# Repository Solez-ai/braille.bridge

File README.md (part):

<div align="center">

# BrailleBridge (BB1)

**Open-Source Bilingual English & Bharati Bangla Wireless Mechanical Braille Chording System**

*Hardware v3 · BB1 Wiring Board PCB v4 · Decode-on-Release ESP32 Firmware · PyQt6 Desktop Teacher Suite · Kotlin Jetpack Compose Android App · Web Bluetooth & Web Serial Console*

<p>

</p>

<p>
  <a href="https://brailebridge.vercel.app/"><strong>Live Web Application</strong></a> ·
  <a href="https://solez-ai.mintlify.app"><strong>Technical Documentation</strong></a> ·
  <a href="https://github.com/solez-ai/braille.bridge/releases/latest"><strong>Download Desktop EXE & Android APK</strong></a> ·
  <a href="hardware/bb1_wiring_board_v4/exports/jlcpcb_gerbers_v4.zip"><strong>JLCPCB Gerber Package (v4)</strong></a> ·
  <a href="BrailleBridge_Technical_Documentation.pdf"><strong>Engineering Monograph (PDF)</strong></a>
</p>

<br />

</div>

---

## Table of Contents

1. [Executive Overview](#1-executive-overview)
2. [Comparative Benchmark Against Legacy Assistive Systems](#2-comparative-benchmark-against-legacy-assistive-systems)
3. [Institutional Field Testing & Validation](#3-institutional-field-testing--validation)
   - [3.1 BERDO — Blind Education and Rehabilitation Development Organization](#31-berdo--blind-education-and-rehabilitation-development-organization)
   - [3.2 University of Dhaka — Resource Centre for the Visually Impaired Students (Co-Sponsored by Sightsavers)](#32-university-of-dhaka--resource-centre-for-the-visually-impaired-students-co-sponsored-by-sightsavers)
4. [Mechanical Hardware & 3D-Printed Wedge Enclosure (v3)](#4-mechanical-hardware--3d-printed-wedge-enclosure-v3)
   - [4.1 Physical Layout & Ergonomic Geometry](#41-physical-layout--ergonomic-geometry)
   - [4.2 Multi-Angle Hardware Gallery](#42-multi-angle-hardware-gallery)
   - [4.3 Bill of Materials (BOM) & Direct GPIO Architecture](#43-bill-of-materials-bom--direct-gpio-architecture)
5. [Custom Commercial PCB — BB1 Wiring Board v4 (KiCad 10)](#5-custom-commercial-pcb--bb1-wiring-board-v4-kicad-10)
   - [5.1 Raytraced 3D Renders & 2D Copper Composite](#51-raytraced-3d-renders--2d-copper-composite)
   - [5.2 Full KiCad 10 Schematic Diagram](#52-full-kicad-10-schematic-diagram)
   - [5.3 Dual-Mode Buck-Boost Power Architecture & Global Manufacturing Flexibility](#53-dual-mode-buck-boost-power-architecture--global-manufacturing-flexibility)
   - [5.4 Physical Stackup, Netlist Verification & Pin Allocation](#54-physical-stackup-netlist-verification--pin-allocation)
6. [ESP32 Firmware & Chording State Machine](#6-esp32-firmware--chording-state-machine)
   - [6.1 Six-Dot Bitmask Encoding](#61-six-dot-bitmask-encoding)
   - [6.2 Decode-on-Release Algorithm & Temporal Guards](#62-decode-on-release-algorithm--temporal-guards)
   - [6.3 Dual-Transport ASCII vs. Multi-Byte UTF-8 Rule](#63-dual-transport-ascii-vs-multi-byte-utf-8-rule)
   - [6.4 Structured Telemetry & Host Command Protocol](#64-structured-telemetry--host-command-protocol)
7. [Bilingual Grade 1 English & Bharati Bangla Dictionaries](#7-bilingual-grade-1-english--bharati-bangla-dictionaries)
8. [Multi-Platform Software Ecosystem](#8-multi-platform-software-ecosystem)
   - [8.1 System Architecture](#81-system-architecture)
   - [8.2 Native Desktop Teacher Suite (Python / PyQt6 / Bleak / WinRT / PySerial)](#82-native-desktop-teacher-suite-python--pyqt6--bleak--winrt--pyserial)
   - [8.3 Android Companion Application (Kotlin 2.2 / Jetpack Compose / Room)](#83-android-companion-application-kotlin-22--jetpack-compose--room)
   - [8.4 Web Platform, Interactive 3D/2D PCB Inspector & Virtual Chord Pad](#84-web-platform-interactive-3d2d-pcb-inspector--virtual-chord-pad)
9. [Repository Structure](#9-repository-structure)
10. [Build, Flash & Fabrication Guide](#10-build-flash--fabrication-guide)
11. [License & Citation](#11-license--citation)

---

## 1. Executive Overview

Across South Asia and the developing world, visually impaired students face a severe Structural Scribal Dependency during high-stakes public and university examinations. Because traditional mechanical Perkins Braillers produce embossed paper scripts that sighted examiners cannot read—and commercial refreshable Braille displays cost between **$1,500 and $3,500+ USD**—students are forced to dictate answers verbally to human scribes. A human scribe filters the student's literacy, spelling accuracy, mathematical notation, and pacing through a third party.

**BrailleBridge (BB1)** eliminates scribal dependency for less than **$15 USD** in total hardware cost (**~$11.70 USD** in raw components).

1. **Tactile Mechanical Input**: The student types standard 6-dot Braille chords on eight full-travel **Outemu Red linear mechanical switches** (`45 gf` actuation force, `2.0 mm` pre-travel, `4.0 mm` total travel, `50M`-cycle rating) housed in a tool-free, 3D-printed PLA wedge chassis with an ergonomic `7.1°` typing slope.
2. **Deterministic Decode-on-Release Engine**: An **ESP32-WROOM-32** dual-core microcontroller samples all eight switch channels directly via internal pull-up resistors (`INPUT_PULLUP`), accumulating a 6-bit chord bitmask (`0x01`–`0x3F`) across the downstroke and decoding the complete chord at the exact microsecond all keys are released (`15 ms` contact-bounce filter, live-tunable `5–50 ms`, supporting **100+ WPM** rapid chording).
3. **Bilingual Grade 1 English & Bharati Bangla**: A single `500 ms` hold of Dots `4+5+6` toggles between standard **Grade 1 English Braille** and **6-dot Bharati Bangla Braille** (স্বরবর্ণ vowels, ব্যঞ্জনবর্ণ consonants, কার dependent vowel signs via `Shift` layer, numerals `0–9`, and mathematical operators), totaling **54 base mappings** plus shifted layers.
4. **Simultaneous Sighted & Auditory Output**: Every decoded chord streams simultaneously over **Bluetooth Low Energy HID**, **BLE Nordic UART Service (NUS)**, and **USB Serial (`115200` baud)** to sighted teachers' screens (in print English, Bangla, or **128 real-time translated languages**) while local offline Text-to-Speech (`pyttsx3` / SAPI5 / Android TTS / Web Speech API) speaks every letter, word, and UI event back to the blind student.

---

## 2. Comparative Benchmark Against Legacy Assistive Systems

| Engineering Metric | Human Exam Scribe | Mechanical Perkins Brailler | Commercial Refreshable Display | **BrailleBridge (BB1 v3 / PCB v4)** |
| :--- | :--- | :--- | :--- | :--- |
| **Unit Cost (USD)** | Recurring per-exam fee | $750 – $950 USD | $1,500 – $3,500+ USD | **~$11.70 BOM (<$15 complete)** |
| **Student Independence** | None (verbal dictation) | High (embossed paper only) | High | **100% direct student authorship** |
| **Sighted Teacher Readability** | Sighted scribe handwriting | Unreadable without Braille training | Requires proprietary host software | **Instant live print text + 128-language translation** |
| **Bharati Bangla + English** | Depends on scribe fluency | Manual embossing only | Rarely supported natively | **Hardware chord toggle (`Dots 4+5+6` hold, `500 ms`)** |
| **Acoustic Noise Profile** | Verbal noise (requires isolated room) | ~75–80 dBA impact embossing | ~55 dBA piezoelectric pins | **~42 dBA silent linear switches (mainstream classroom safe)** |
| **Chording Speed Ceiling** | Limited by dictation speed | ~40–60 WPM mechanical return | ~60–80 WPM | **100+ WPM (`15 ms` decode-on-release state machine)** |
| **Power Architecture** | N/A | Purely mechanical | Proprietary sealed Li-Po pack | **USB-C + 4×AA (Direct Bypass or 5 V Buck-Boost Module)** |
| **Repairability & CAD/PCB** | N/A | Factory specialist overhaul | Sealed proprietary assembly | **100% Open-Source (GPL-3.0 STL + KiCad 10 PCB + Firmware)** |

---

## 3. Institutional Field Testing & Validation

BrailleBridge was evaluated directly in institutional environments in Dhaka, Bangladesh with visually impaired learners, university students, and assistive education pioneers.

### 3.1 BERDO — Blind Education and Rehabilitation Development Organization

Field validation was conducted at the **Blind Education and Rehabilitation Development Organization (BERDO)** headquarters in Rupnagar, Mirpur, Dhaka, under the supervision of BERDO Founder and Executive Director **Md. Saidul Huq**—recipient of the **2026 Independence Award (Swadhinata Puruskar)**, Bangladesh's highest civilian state honor, and the **2023 Ekushey Padak**. Visually impaired students and educators tested the 8-switch mechanical tactile profile, bilingual Bharati Bangla chording, and real-time voice synthesis.

<div align="center">
<table>
  <tr>
    <td align="center" width="50%">
      
      <br />
      <sub><strong>Fig 3.1a:</strong> Institutional demonstration with Md. Saidul Huq (Founder &amp; Executive Director, BERDO; 2026 Swadhinata Puruskar &amp; 2023 Ekushey Padak laureate).</sub>
    </td>
    <td align="center" width="50%">
      
      <br />
      <sub><strong>Fig 3.1b:</strong> Tactile evaluation of the 8-switch mechanical Perkins layout inside the BERDO Braille library in Mirpur, Dhaka.</sub>
    </td>
  </tr>
  <tr>
    <td align="center" width="50%">
      
      <br />
      <sub><strong>Fig 3.1c:</strong> Real-time bilingual English and Bharati Bangla chording trial with live desktop telemetry.</sub>
    </td>
    <td align="center" width="50%">
      
      <br />
      <sub><strong>Fig 3.1d:</strong> Assessing Outemu Red 45 gf actuation consistency and decode-on-release responsiveness.</sub>
    </td>
  </tr>
</table>

<p>
  
</p>
</div>

### 3.2 University of Dhaka — Resource Centre for the Visually Impaired Students (Co-Sponsored by Sightsavers)

BrailleBridge was benchmarked side-by-side against mechanical Perkins Braillers at the **Resource Centre for the Visually Impaired Students** inside the **Dhaka University Central Library** (Kazi Nazrul Islam Ave, Dhaka). Established in **2007** and jointly sponsored by **Dhaka University Library** and **Sightsavers**, the Resource Centre serves visually impaired undergraduates and researchers across the university.

<div align="center">
<table>
  <tr>
    <td align="center" width="50%">
      
      <br />
      <sub><strong>Fig 3.2a:</strong> Resource Centre for the Visually Impaired Students at Dhaka University Central Library (Jointly Sponsored by Dhaka University Library &amp; Sightsavers).</sub>
    </td>
    <td align="center" width="50%">
      
      <br />
      <sub><strong>Fig 3.2b:</strong> Direct ergonomic and acoustic benchmark of BrailleBridge BB1 alongside a mechanical Perkins Brailler at Dhaka University.</sub>
    </td>
  </tr>
  <tr>
    <td align="center" width="50%">
      
      <br />
      <sub><strong>Fig 3.2c:</strong> Visually impaired student testing wireless 6-dot chording and auditory TTS confirmation at the Dhaka University Resource Centre.</sub>
    </td>
    <td align="center" width="50%">
      
      <br />
      <sub><strong>Fig 3.2d:</strong> Guided finger-placement transition from heavy mechanical embossing levers to low-force 45 gf linear mechanical switches.</sub>
    </td>
  </tr>
</table>

<p>
  
</p>
</div>

---

## 4. Mechanical Hardware & 3D-Printed Wedge Enclosure (v3)

### 4.1 Physical Layout & Ergonomic Geometry

The BB1 v3 enclosure (`180 mm × 80 mm` footprint, tapering from `30 mm` front wall height to `40 mm` rear wall height) forms a `7.1°` angled wedge engineered for neutral wrist posture during extended exam sessions. The top plate mounts **eight `14.0 × 14.0 mm` MX-compatible mechanical switch cutouts** arranged in a symmetric split-hand Perkins Braille arc:

```text
+-----------------------------------------------------------------------+
|                       REAR INTEGRATED HINGE                           |
|                                                                       |
|     [ Dot 3 ]   [ Dot 2 ]   [ Dot 1 ]   [ Dot 4 ]   [ Dot 5 ]   [ Dot 6 ]
|      GPIO 27     GPIO 14     GPIO 12     GPIO 26     GPIO 25     GPIO 33
|      (Ring L)   (Middle L)  (Index L)   (Index R)   (Middle R)  (Ring R)
|                                                                       |
|                   [ SPACE ]               [ SHIFT / BKSP ]            |
|                    GPIO 32                    GPIO 23                 |
|                   (Thumb L)                  (Thumb R)                |
|                                                                       |
|             [ SNAP LATCH L ]             [ SNAP LATCH R ]             |
+-----------------------------------------------------------------------+
```

- **Zero External Indicator LEDs**: In keeping with blind-first hardware design, the BB1 v3 architecture eliminates physical indicator LEDs and current-limiting resistor harnesses entirely. All operational feedback (character readout, backspace confirmation, language switching, capital lock state, and BLE pairing status) is delivered through multi-platform auditory speech synthesis and tactile landmarking.
- **Clamshell Serviceability**: A print-in-place rear hinge (`2.2 mm` filament/steel pin) paired with dual front snap latches allows teachers or technicians to open the top plate in seconds without removing screws.
- **Underside Tool-Free `4×AA` Battery Bay**: A drop-out bottom hatch (`120 × 62 mm`) provides immediate external access to the `4×AA` battery holder while isolating the internal PCB cavity.

### 4.2 Multi-Angle Hardware Gallery

<div align="center">
<table>
  <tr>
    <td align="center" width="50%">
      
      <br />
      <sub><strong>Fig 4.2a:</strong> Top isometric render showing the 6-dot ergonomic finger arc and dual thumb modifier keys (`SPACE` and `SHIFT / BKSP`).</sub>
    </td>
    <td align="center" width="50%">
      
      <br />
      <sub><strong>Fig 4.2b:</strong> Front elevation detailing the Outemu Red keycap profile and dual front snap-latch seam.</sub>
    </td>
  </tr>
  <tr>
    <td align="center" width="50%">
      
      <br />
      <sub><strong>Fig 4.2c:</strong> Quarter-angle view highlighting the `30 mm` to `40 mm` (`7.1°`) ergonomic wedge slope.</sub>
    </td>
    <td align="center" width="50%">
      
      <br />
      <sub><strong>Fig 4.2d:</strong> Close-up of the `14 × 14 mm` plate-mounted Outemu Red linear switches (`45 gf` actuation).</sub>
    </td>
  </tr>
  <tr>
    <td align="center" width="50%">
      
      <br />
      <sub><strong>Fig 4.2e:</strong> Rear elevation showing the 3-knuckle clamshell hinge and slide power switch cutout (`12 × 6 mm`).</sub>
    </td>
    <td align="center" width="50%">
      
      <br />
      <sub><strong>Fig 4.2f:</strong> Orthographic top plan of the `180 × 80 mm` switch deck (`23 mm` center-to-center key spacing).</sub>
    </td>
  </tr>
  <tr>
    <td align="center" width="50%">
      
      <br />
      <sub><strong>Fig 4.2g:</strong> Underside tool-free `4×AA` drop-out battery compartment (`120 × 62 mm`).</sub>
    </td>
    <td align="center" width="50%">
      
      <br />
      <sub><strong>Fig 4.2h:</strong> Left side profile showing the `14 × 8 mm` USB-C programming/serial access window.</sub>
    </td>
  </tr>
</table>
</div>

### 4.3 Bill of Materials (BOM) & Direct GPIO Architecture

Every switch is wired as a dedicated SPST normally-open contact between an ESP32 GPIO pin configured as `INPUT_PULLUP` (internal `~45 kΩ` pull-up to `3.3 V`) and the common ground plane (`GND`). Because no row/column diode multiplexing matrix is used, **8-key rollover (NKRO) is physically guaranteed with zero ghosting**.

| Switch / Module | Physical Role | Anatomical Finger | ESP32 GPIO | Active Logic | Electrical Configuration |
| :--- | :--- | :--- | :--- | :--- | :--- |
| **Dot 1 (`D1`)** | Left Column, Top Dot | Left Index | `GPIO 12` | Active-LOW (`0 V`) | Direct `INPUT_PULLUP` (`0b000001` / `0x01`) |
| **Dot 2 (`D2`)** | Left Column, Middle Dot | Left Middle | `GPIO 14` | Active-LOW (`0 V`) | Direct `INPUT_PULLUP` (`0b000010` / `0x02`) |
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
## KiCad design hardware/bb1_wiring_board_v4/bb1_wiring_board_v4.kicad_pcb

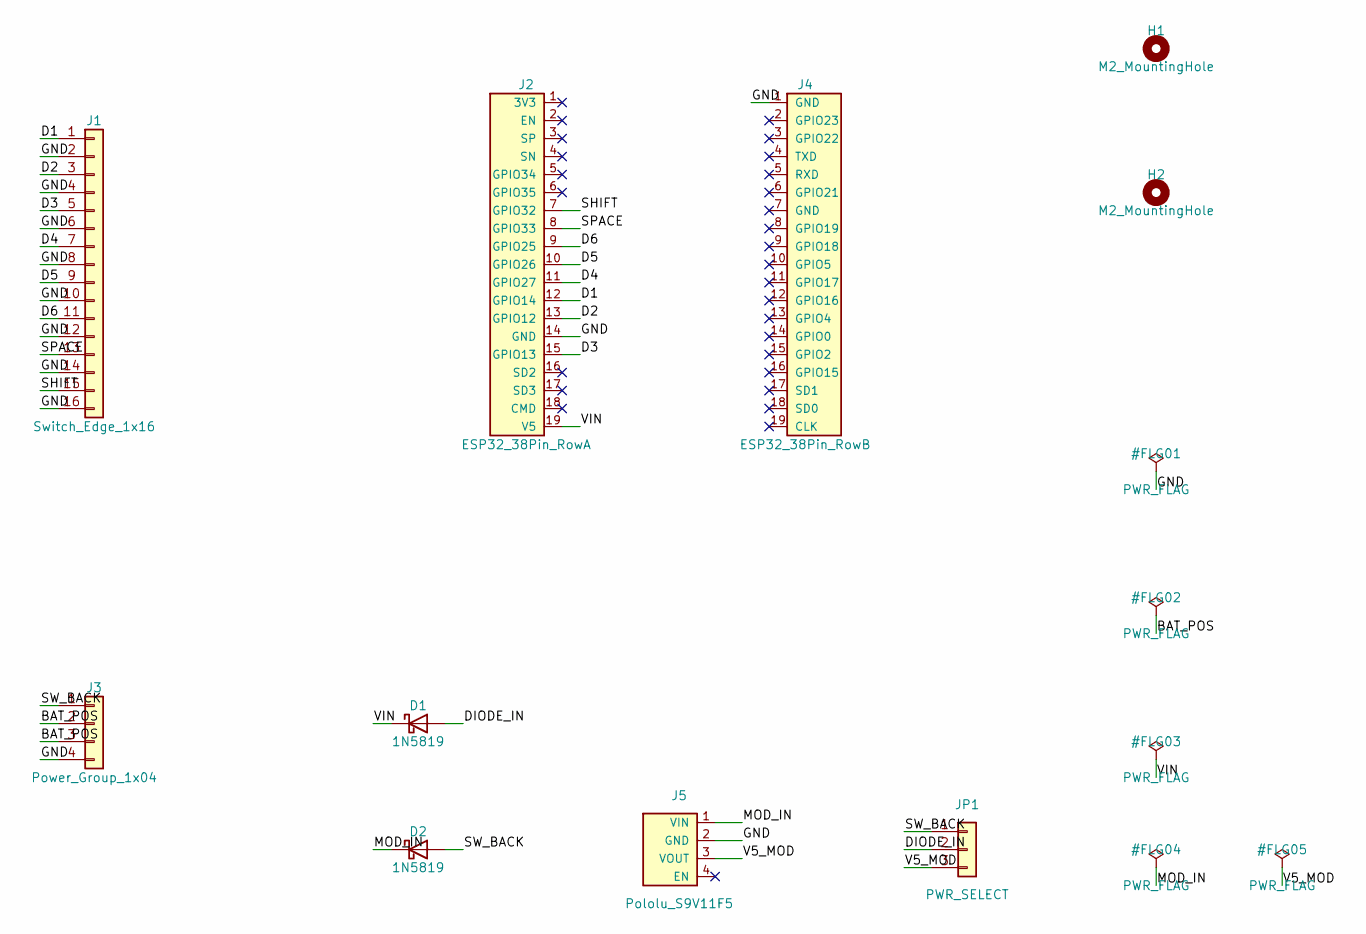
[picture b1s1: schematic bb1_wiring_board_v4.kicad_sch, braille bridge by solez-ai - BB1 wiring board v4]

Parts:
D1, D2: 1N5819; D_DO-41_SOD81_P10.16mm_Horizontal
H1, H2: M2_MountingHole; MountingHole_2.2mm_M2
J1: Switch_Edge_1x16; PinHeader_1x16_P2.54mm_Vertical
J2: ESP32_38Pin_RowA; PinSocket_1x19_P2.54mm_Vertical
J3: Power_Group_1x04; PinHeader_1x04_P2.54mm_Vertical
J4: ESP32_38Pin_RowB; PinSocket_1x19_P2.54mm_Vertical
J5: Pololu_S9V11F5; PinSocket_1x04_P2.54mm_Vertical
JP1: PWR_SELECT; PinHeader_1x03_P2.54mm_Vertical

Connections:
/BAT_POS: J3.2, J3.3
/D1: J1.1, J2.12 (GPIO14)
/D2: J1.3, J2.13 (GPIO12)
/D3: J1.5, J2.15 (GPIO13)
/D4: J1.7, J2.11 (GPIO27)
/D5: J1.9, J2.10 (GPIO26)
/D6: J1.11, J2.9 (GPIO25)
/DIODE_IN: D1.2 (A), JP1.2
/GND: J1.2, J1.4, J1.6, J1.8, J1.10, J1.12, J1.14, J1.16, J2.14 (GND), J3.4, J4.1 (GND), J5.2 (GND)
/MOD_IN: D2.1 (K), J5.1 (VIN)
/SHIFT: J1.15, J2.7 (GPIO32)
/SPACE: J1.13, J2.8 (GPIO33)
/SW_BACK: D2.2 (A), J3.1, JP1.1
/V5_MOD: J5.3 (VOUT), JP1.3
/VIN: D1.1 (K), J2.19 (V5)

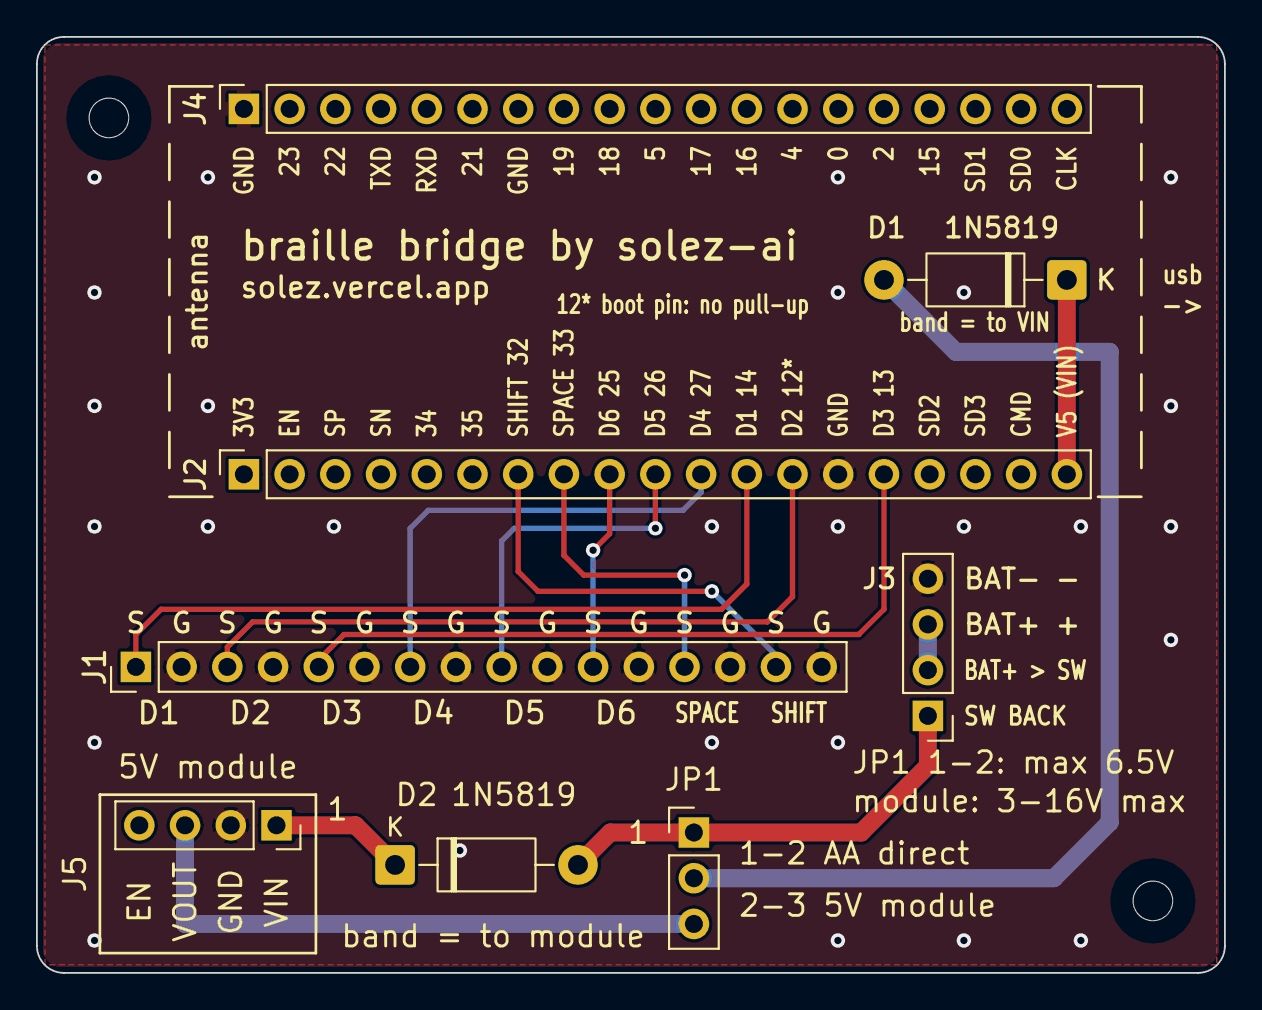
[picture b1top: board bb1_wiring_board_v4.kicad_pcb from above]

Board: 2 copper layers, 66.0 x 52.0 mm, 10 parts (0 on the bottom side), 15 nets.

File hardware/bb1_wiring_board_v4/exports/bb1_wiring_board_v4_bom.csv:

Designator,Qty,Value_Part,Package_Footprint,Description,DNP
"D1, D2",2,1N5819,Diode_THT:D_DO-41_SOD81_P10.16mm_Horizontal,40V 1A Schottky Barrier Diode (D1: band to VIN; D2: band to module),No
J1,1,Conn_01x16_Pin,Connector_PinHeader_2.54mm:PinHeader_1x16_P2.54mm_Vertical,2.54mm 1x16 vertical male pin header (8x SIG+GND switch pairs),No
"J2, J4",2,ESP32_38Pin_RowA / RowB (1x19 Female Socket),Connector_PinSocket_2.54mm:PinSocket_1x19_P2.54mm_Vertical,2.54mm 1x19 vertical female socket header for 38-pin ESP32 DevKit (20.3mm row spacing),No
J3,1,Conn_01x04_Pin,Connector_PinHeader_2.54mm:PinHeader_1x04_P2.54mm_Vertical,"2.54mm 1x04 vertical male pin header (BAT-, BAT+, BAT+>SW, SW BACK)",No
J5,1,1x04 Female Socket (for Pololu S9V11F5 5V Buck-Boost),Connector_PinSocket_2.54mm:PinSocket_1x04_P2.54mm_Vertical,"2.54mm 1x04 vertical female socket (pin 1=VIN, 2=GND, 3=VOUT, 4=EN); plug-in 5V module",No
JP1,1,Conn_01x03_Pin + 1x 2.54mm Jumper Cap (Shunt),Connector_PinHeader_2.54mm:PinHeader_1x03_P2.54mm_Vertical,2.54mm 1x03 vertical male header + 1x shunt cap (1-2: AA direct; 2-3: 5V module),No
"H1, H2",2,MountingHole_2.2mm_M2,MountingHole:MountingHole_2.2mm_M2,"M2 unplated mounting hole (2.2mm drill, 5mm copper keepout)",Mechanical

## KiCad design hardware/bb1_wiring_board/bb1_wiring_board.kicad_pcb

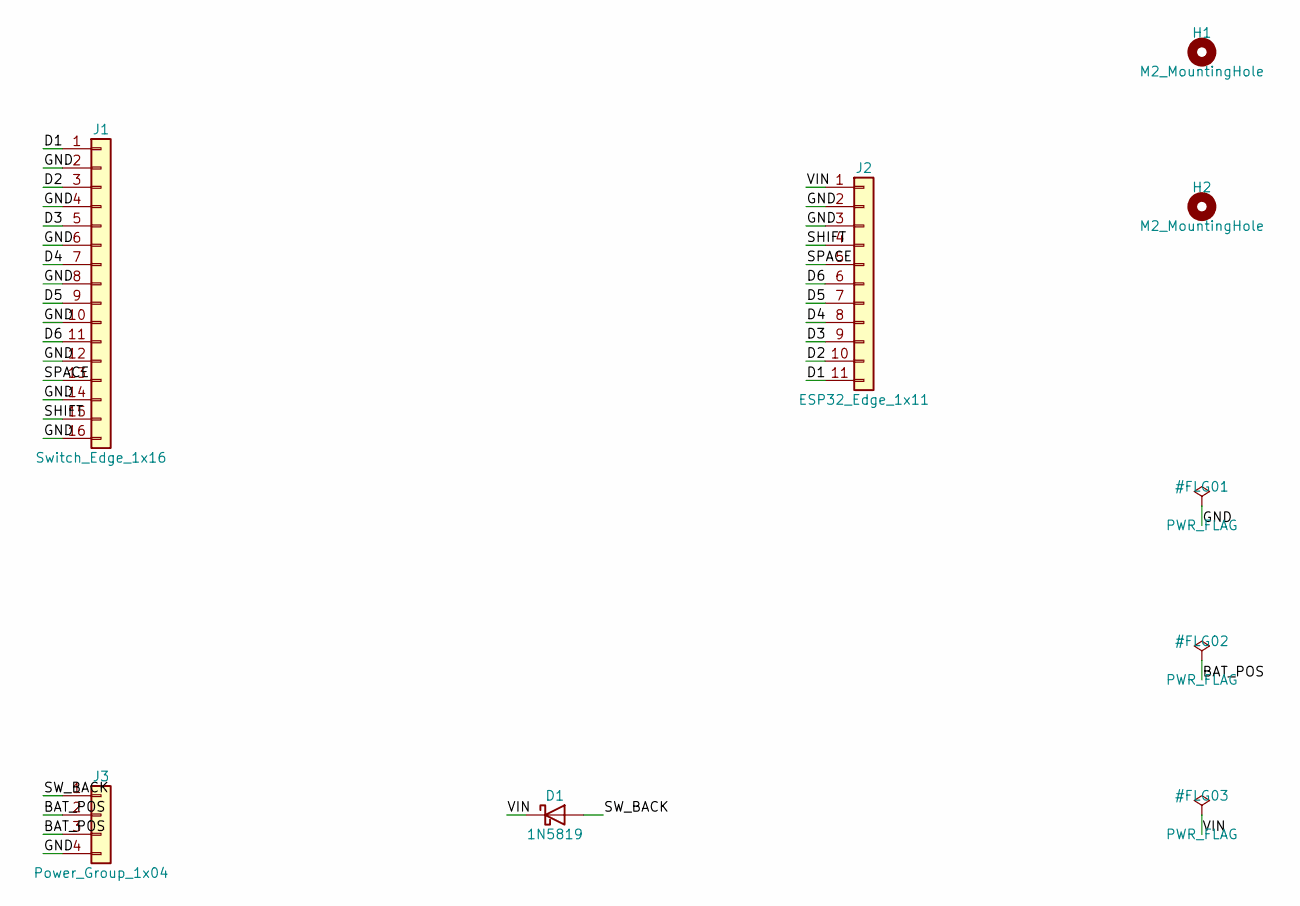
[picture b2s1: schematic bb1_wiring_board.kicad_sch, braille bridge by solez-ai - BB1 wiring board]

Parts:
D1: 1N5819; D_DO-41_SOD81_P10.16mm_Horizontal
H1, H2: M2_MountingHole; MountingHole_2.2mm_M2
J1: Switch_Edge_1x16; PinHeader_1x16_P2.54mm_Horizontal
J2: ESP32_Edge_1x11; PinHeader_1x11_P2.54mm_Horizontal
J3: Power_Group_1x04; PinHeader_1x04_P2.54mm_Horizontal

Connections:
/BAT_POS: J3.2, J3.3
/D1: J1.1, J2.11
/D2: J1.3, J2.10
/D3: J1.5, J2.9
/D4: J1.7, J2.8
/D5: J1.9, J2.7
/D6: J1.11, J2.6
/GND: J1.2, J1.4, J1.6, J1.8, J1.10, J1.12, J1.14, J1.16, J2.2, J2.3, J3.4
/SHIFT: J1.15, J2.4
/SPACE: J1.13, J2.5
/SW_BACK: D1.2 (A), J3.1
/VIN: D1.1 (K), J2.1

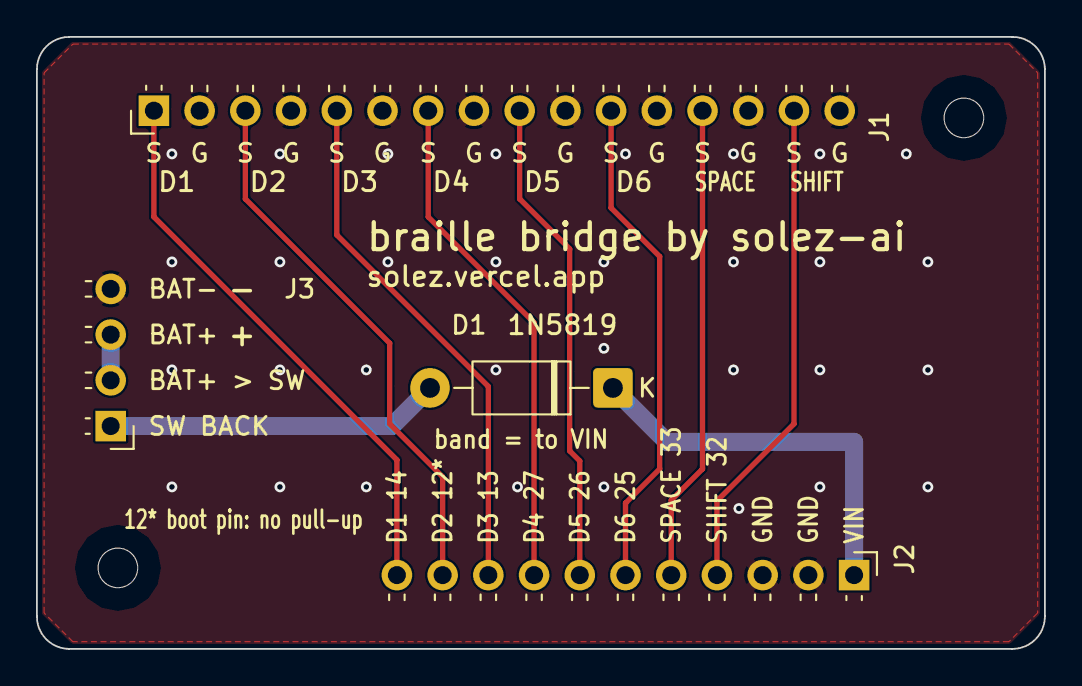
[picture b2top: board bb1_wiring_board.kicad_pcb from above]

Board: 2 copper layers, 56.0 x 34.0 mm, 6 parts (0 on the bottom side), 12 nets.

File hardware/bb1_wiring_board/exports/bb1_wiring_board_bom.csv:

Reference,Quantity,Value,Description,Footprint,Notes
J1,1,PinHeader_1x16_P2.54mm_Horizontal,16-pin 2.54mm pitch male right-angle pin header (Switch Edge),Connector_PinHeader_2.54mm:PinHeader_1x16_P2.54mm_Horizontal,Pins 1-16 = 8x (SIG GND) pairs D1..SHIFT
J2,1,PinHeader_1x11_P2.54mm_Horizontal,11-pin 2.54mm pitch male right-angle pin header (ESP32 Edge),Connector_PinHeader_2.54mm:PinHeader_1x11_P2.54mm_Horizontal,Pins 11..1 = D1..SHIFT GND GND VIN
J3,1,PinHeader_1x04_P2.54mm_Horizontal,4-pin 2.54mm pitch male right-angle pin header (Power Group),Connector_PinHeader_2.54mm:PinHeader_1x04_P2.54mm_Horizontal,Pins 4..1 = BAT- BAT+ BAT+>SW SW BACK
D1,1,1N5819,1N5819 Schottky Barrier Diode 40V 1A DO-41 Axial Horizontal,Diode_THT:D_DO-41_SOD81_P10.16mm_Horizontal,Pin 1 (K/Band)=VIN Pin 2 (A)=SW_BACK
H1 H2,2,MountingHole_2.2mm_M2,M2 Non-Plated Mounting Hole 2.2mm drill (BOM/PNP excluded),MountingHole:MountingHole_2.2mm_M2,Drilled PCB holes only (5mm copper keepout)

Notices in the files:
README.md:
BrailleBridge is open-source hardware and software released under the **[GNU General Public License v3.0 (GPL-3.0)](LICENSE)**. Schools, NGOs, ministries of education, and assistive-technology fabricators are explicitly encouraged to manufacture, localize, and deploy BrailleBridge without royalty fees.
